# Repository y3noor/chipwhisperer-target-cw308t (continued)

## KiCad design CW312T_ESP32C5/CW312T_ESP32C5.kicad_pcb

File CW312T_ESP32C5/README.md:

# CW312T ESP32-C5, rev 01

This 3.3 V CW312 card uses the Espressif ESP32-C5-WROOM-1-N16R8. The module has 16 MB of flash, 8 MB of quad SPI PSRAM, and a PCB antenna. Espressif lists this exact part as a production variant in table 1-1. Open the KiCad 10 project to edit the schematic and PCB. The BOM and CW312 contact list are in `bom.csv` and `cw312-pinout.csv`.

## Power and current

J1 is the only power input. Connect regulated 3.3 V to J1.1 and ground to J1.2. Use a supply that can deliver at least 1 A for bench tests. Keep voltage at TP2 within 3.0 to 3.6 V, including during startup and radio activity.

The CW313 passes the capture unit's 3.3 V supply to A5. Husky specifies 200 mA at its target connector. The C5 module datasheet lists up to 403 mA peak for 5 GHz Wi-Fi and 313 mA for 2.4 GHz Wi-Fi. A first-order charging estimate for 22 µF of input capacitance is 73 mA for a 1 ms, 3.3 V ramp. A faster ramp can exceed 200 mA before the device starts. The card leaves A5, the other CW313 supply pins, and both SMA shunt pins open. There is no path from J1 to those supplies. A26 supplies the debugger's voltage-sense input through R5. Use a debugger that takes a voltage reference at this pin. Leave B10 open.

R1 is the fitted 0 Ω series link. Remove R1 with power off and connect an ammeter between TP1 (source side) and TP2 (load side). The meter includes the module, its decoupling, bias resistors, and any current drawn at the debugger reference. It excludes the bench supply's own current. Check the voltage at TP2 under load. Restore R1 after the test.

Signal pins connect directly to the module. Before energizing the card, power the CW313 host and set its connected I/O to high impedance. Enable host and probe drivers only after the target rail is up. Put the drivers back in high impedance or disconnect the cable before removing target power. This procedure prevents current through signal protection diodes when one side is off.

## Bring-up

1. Keep all power off. Align the key with the CW313 slot. The module side faces the CW313 component side. Check that the card is seated and the antenna projects away from the baseboard.
2. Connect bench power at J1. Check TP1, TP2, and TP3. Confirm that EN at TP4 rises after the supply. Press RESET and confirm that TP4 goes low.
3. Connect a 3.3 V UART adapter to J2. Use J2.1 for ground, J2.2 for target TX, and J2.3 for target RX. TP5 and TP6 expose those signals. When the adapter drives RX, keep Husky's UART TX at high impedance. Hold BOOT, tap RESET, and release BOOT to enter ROM download. Use Espressif esptool with the ESP32-C5 target. Tap RESET with BOOT released to run the image.
4. For USB Serial/JTAG, solder a short USB full-speed data cable directly to J3. J3.1 is ground, J3.2 is D−, and J3.3 is D+. Insulate the cable's VBUS wire. Power J1 before attaching the cable to the host. Use the ESP32-C5 built-in USB-JTAG OpenOCD configuration. The optional pin header is DNP.
5. For external pad JTAG, the four signals are on the CW313 JTAG header. Use the target-side reference on A26 and local RESET. The module defaults to USB Serial/JTAG. GPIO7 is pulled low for the external pad selection if EFUSE_JTAG_SEL_ENABLE is set. Check the device eFuse state before selecting this debug path. GPIO28 is pulled high for SPI flash boot. GPIO27 is pulled high so holding GPIO28 low at reset selects Joint Download Boot 0 for UART or USB. GPIO26 uses its internal default.
6. Configure GPIO6 as an output for the trigger on CW312 B19. Set CW313 JP2 to GPIO4. Keep the baseboard end configured as an input.

## Mechanical and fabrication checks

The CW312 finger sides, 1.00 mm pitch, 3.00 mm pitch across the key, 0.70 × 4.20 mm lands, and 34.30 mm tongue span follow the template and match the RP2350 contact pattern. The 1.60 mm card thickness matches the existing card fabrication notes and the Samtec -02 slot. The insertion tip chamfers are 0.50 mm in the board plane. Fit the card like the RP2350 reference, with pin B1 on the component side. This is the CW312 pinout.

The template outline is 58.675 × 53.691 mm. The far edge has a 1 mm recess to let the complete 6.5 mm antenna region overhang. The assembly has no card substrate under the antenna, and an all-copper keepout extends around it. Other components start above the slot contact area. In the nominal mated position, the antenna is more than 40 mm from the slot and farther from the CW313 copper. Keep cables, fixtures, and metal at least 15 mm away from the antenna. Check this clearance on the actual bench assembly.

Use a four-layer 1.60 mm board with continuous ground copper around the module and beneath the USB pair. Use 0.15 mm minimum trace and clearance, 0.25 mm minimum copper-to-edge clearance, and 0.20 mm minimum plated drill. Use a process that fills and caps the small vias in U1's exposed pad to prevent solder wicking. Specify a flat gold finish on the card contacts. The RP2350 reference uses immersion gold with no thickness bevel. Confirm the slot manufacturer's finish and bevel requirements if ordering for repeated mating. The PCB has no paste on the edge contacts.

KiCad 10.0.6 ERC reports zero violations. DRC reports zero errors, zero unrouted items, and zero schematic parity issues. There are zero DRC warnings. The U1 footprint follows figure 11-1. It uses a single 4.70 mm exposed ground land with nine 1.30 mm paste apertures and twelve thermal vias. The Gerbers and Excellon files represent rev 01. Qualify slot insertion, probe access, USB operation, startup and RF current, and antenna performance on a first article.

## References

- NewAE CW312 template rev 0, `cw312_template.PcbDoc` and `cw312_template_cardedge.SchDoc`, commit `40c337d2c8c15345bab03c9aa2072a23a36ccc3b`. The template license field says TBD.
- NewAE CW312T_RP2350 rev 02, schematic, PCB, fabrication notes, and insertion photo. The project is marked NDA. The KiCad project has newly drawn card geometry. The original Altium files served as dimensional and connectivity references.
- NewAE CW313 rev 02 schematic and PCB, commit `7b689277ca6852fccd195c29525a26640b6296d0`. The schematic title block states CC SA 3.0. [CW313 design files](https://github.com/newaetech/chipwhisperer-target-cw313/tree/7b689277ca6852fccd195c29525a26640b6296d0)
- Samtec PCIE-XXX-02-X-D-RA series drawing, sheet 1 rev C and sheet 2 rev D. [Connector drawing](https://suddendocs.samtec.com/prints/pcie-xxx-02-x-d-ra-mkt.pdf)
- Espressif ESP32-C5-WROOM-1/WROOM-1U datasheet v1.3, sections 3, 4, 6, 9, and 11. Draw the custom module land pattern from figure 11-1. [Module datasheet](https://documentation.espressif.com/esp32-c5-wroom-1_wroom-1u_datasheet_en.pdf)
- Espressif ESP32-C5-DevKitC-1 schematic v1.2, 2025-02-11. Check the reset RC, boot switch, and UART circuit. [DevKit schematic](https://dl.espressif.com/dl/schematics/SCH_ESP32-C5-DevkitC-1_V1.2_20250211.pdf)
- NewAE Husky target connector power limit. [Husky hardware manual](https://rtfm.newae.com/Capture/ChipWhisperer-Husky/)

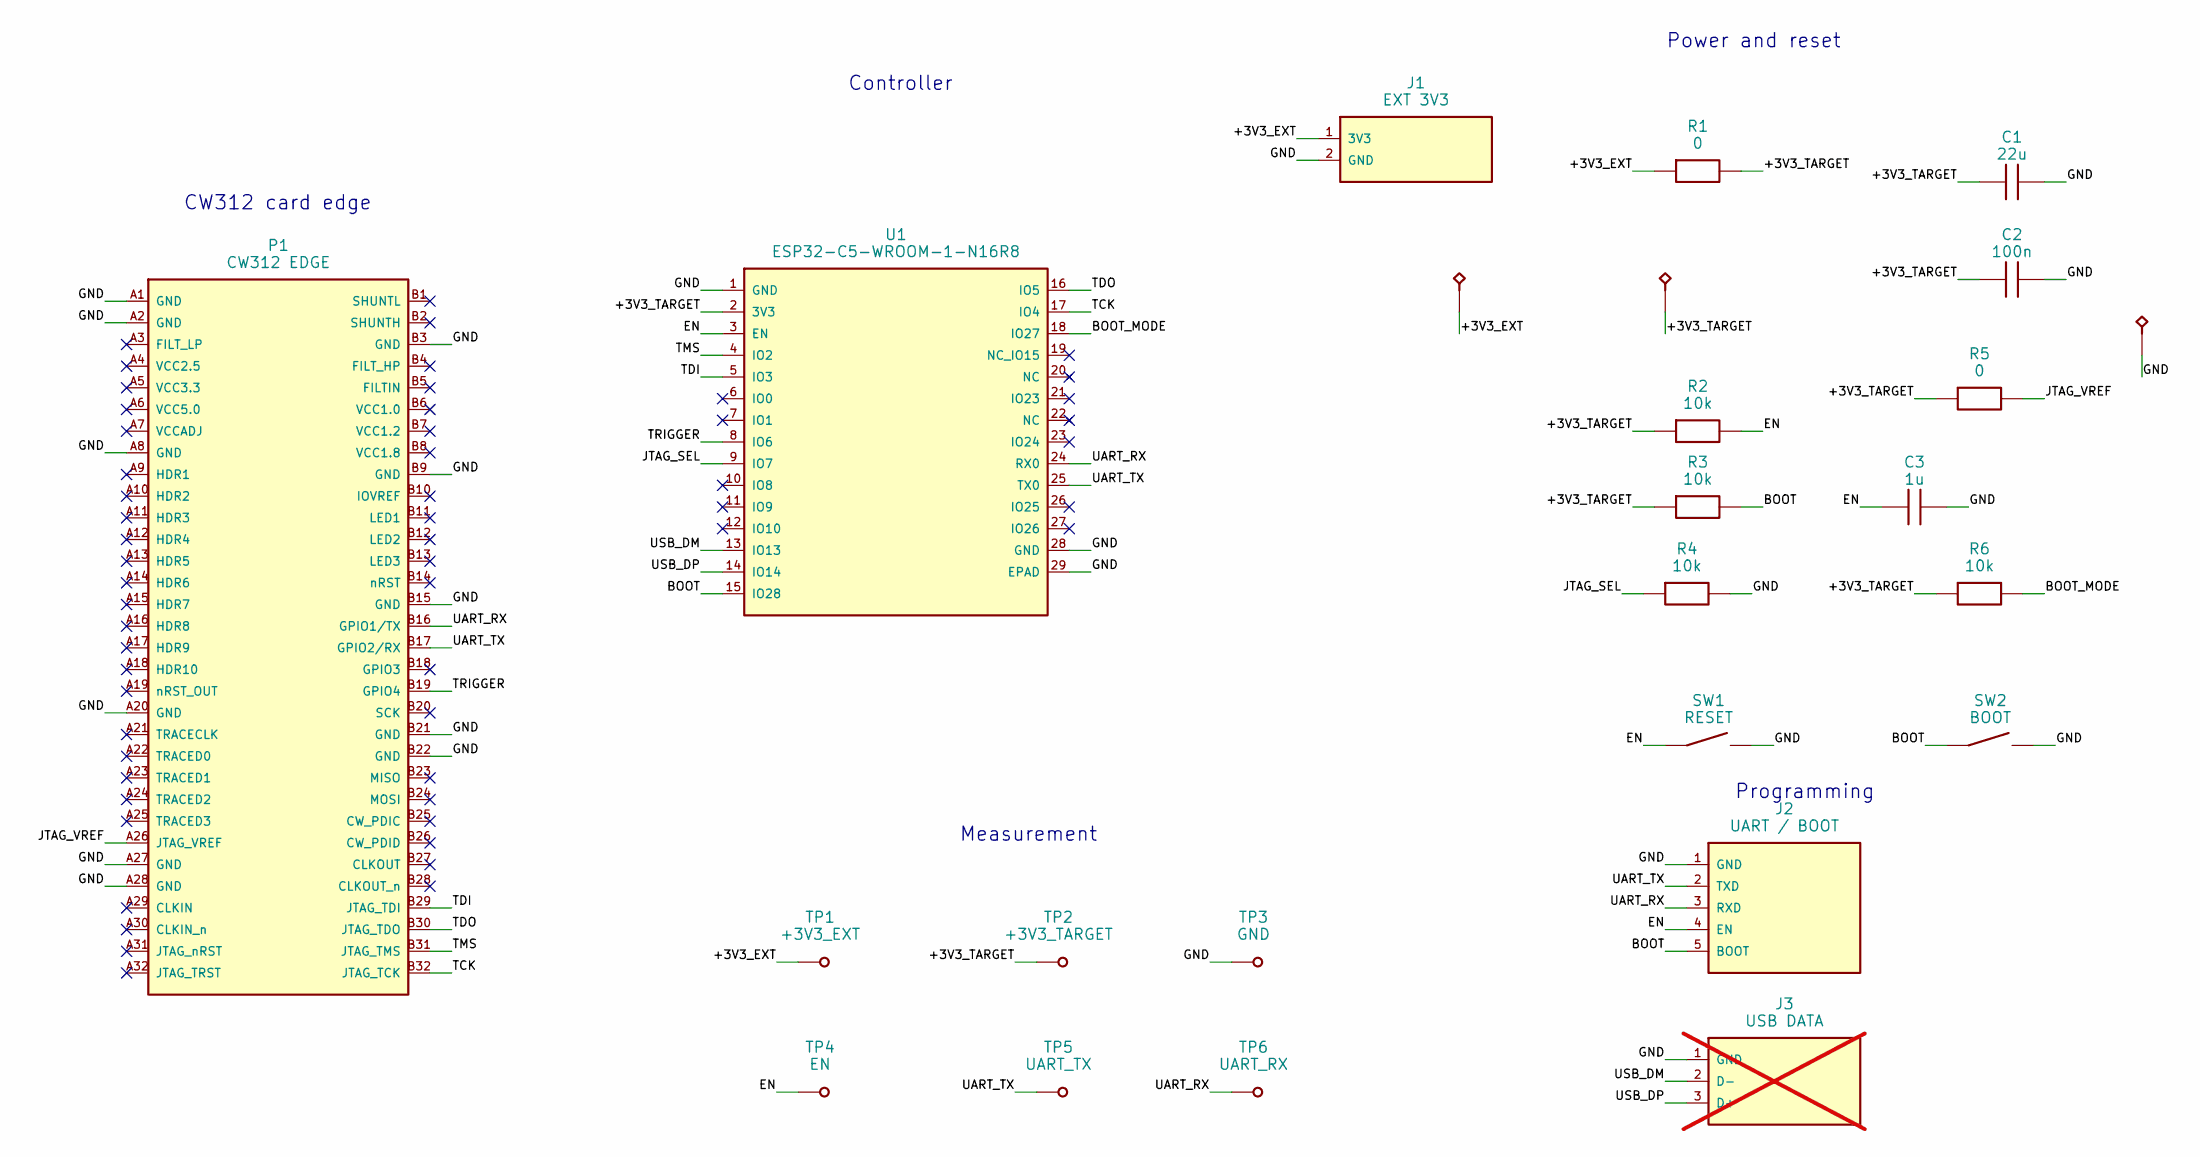
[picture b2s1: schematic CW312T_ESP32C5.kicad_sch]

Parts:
C1: 22u; C_0805_2012Metric
C2: 100n; C_0603_1608Metric
C3: 1u; C_0603_1608Metric
J1: EXT 3V3; PinHeader_1x02_P2.54mm_Vertical
J2: UART / BOOT; PinHeader_1x05_P2.54mm_Vertical
J3: USB DATA; PinHeader_1x03_P2.54mm_Vertical; not fitted
P1: CW312 EDGE; CW312
R1: 0; R_1206_3216Metric
R2, R3, R4, R6: 10k; R_0603_1608Metric
R5: 0; R_0603_1608Metric
SW1: RESET; SW_Tactile_SPST_NO_Straight_CK_PTS636Sx25SMTRLFS
SW2: BOOT; SW_Tactile_SPST_NO_Straight_CK_PTS636Sx25SMTRLFS
TP1: +3V3_EXT; TestPoint_Pad_D1.5mm
TP2: +3V3_TARGET; TestPoint_Pad_D1.5mm
TP3: GND; TestPoint_Pad_D1.5mm
TP4: EN; TestPoint_Pad_D1.5mm
TP5: UART_TX; TestPoint_Pad_D1.5mm
TP6: UART_RX; TestPoint_Pad_D1.5mm
U1: ESP32-C5-WROOM-1-N16R8; ESP32-C5-WROOM-1

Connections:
/+3V3_EXT: J1.1 (3V3), R1.1, TP1.1
/+3V3_TARGET: C1.1, C2.1, R1.2, R2.1, R3.1, R5.1, R6.1, TP2.1, U1.2 (3V3)
/BOOT: J2.5 (BOOT), R3.2, SW2.1, U1.15 (IO28)
/BOOT_MODE: R6.2, U1.18 (IO27)
/EN: C3.1, J2.4 (EN), R2.2, SW1.1, TP4.1, U1.3 (EN)
/GND: C1.2, C2.2, C3.2, J1.2 (GND), J2.1 (GND), J3.1 (GND), P1.A1 (GND), P1.A2 (GND), P1.A8 (GND), P1.A20 (GND), P1.A27 (GND), P1.A28 (GND), P1.B3 (GND), P1.B9 (GND), P1.B15 (GND), P1.B21 (GND), P1.B22 (GND), R4.2, SW1.2, SW2.2, TP3.1, U1.1 (GND), U1.28 (GND), U1.29 (EPAD)
/JTAG_SEL: R4.1, U1.9 (IO7)
/JTAG_VREF: P1.A26 (JTAG_VREF), R5.2
/TCK: P1.B32 (JTAG_TCK), U1.17 (IO4)
/TDI: P1.B29 (JTAG_TDI), U1.5 (IO3)
/TDO: P1.B30 (JTAG_TDO), U1.16 (IO5)
/TMS: P1.B31 (JTAG_TMS), U1.4 (IO2)
/TRIGGER: P1.B19 (GPIO4), U1.8 (IO6)
/UART_RX: J2.3 (RXD), P1.B16 (GPIO1/TX), TP6.1, U1.24 (RX0)
/UART_TX: J2.2 (TXD), P1.B17 (GPIO2/RX), TP5.1, U1.25 (TX0)
/USB_DM: J3.2 (D-), U1.13 (IO13)
/USB_DP: J3.3 (D+), U1.14 (IO14)

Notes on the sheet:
CW312 card edge
Controller
Power and reset
Programming
Measurement

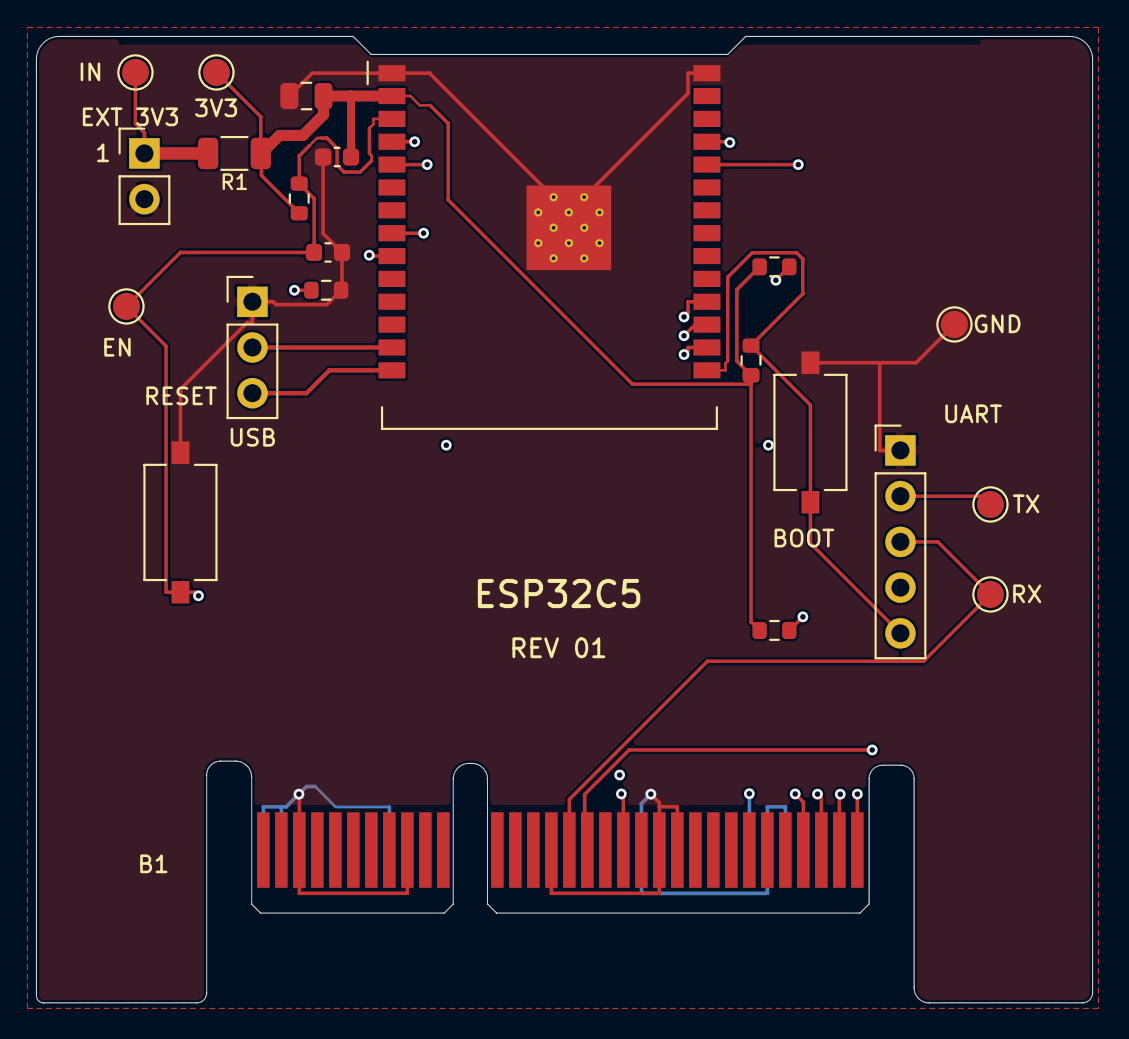
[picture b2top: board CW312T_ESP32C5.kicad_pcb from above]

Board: 4 copper layers, 58.7 x 53.7 mm, 22 parts (0 on the bottom side), 17 nets.

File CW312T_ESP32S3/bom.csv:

Reference,Value,Manufacturer,Manufacturer part number,Package,Qty fitted,DNP
C1,22u,Murata,GRM21BR71A226ME44L,0805,1,No
C2,100n,Murata,GRM188R71H104KA93D,0603,1,No
C3,1u,Murata,GRM188R71C105KA12D,0603,1,No
J1,EXT 3V3,Samtec,TSW-102-07-G-S,2.54 mm THT 1x2,1,No
J2,UART / BOOT,Samtec,TSW-105-07-G-S,2.54 mm THT 1x5,1,No
J3,USB DATA,Samtec,TSW-103-07-G-S,2.54 mm THT 1x3,0,Yes
R1,0,Yageo,RC1206JR-070RL,1206,1,No
R2,10k,Yageo,RC0603FR-0710KL,0603,1,No
R3,10k,Yageo,RC0603FR-0710KL,0603,1,No
R4,10k,Yageo,RC0603FR-0710KL,0603,1,No
R5,0,Yageo,RC0603JR-070RL,0603,1,No
SW1,RESET,C&K,PTS636SK25SMTR LFS,6 x 3.5 mm SMD,1,No
SW2,BOOT,C&K,PTS636SK25SMTR LFS,6 x 3.5 mm SMD,1,No
U1,ESP32-S3-WROOM-1-N16R8,Espressif,ESP32-S3-WROOM-1-N16R8,Castellated module,1,No
